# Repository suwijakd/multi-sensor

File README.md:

# Wearable multi-sensor logger (ESP32-C3)

Firmware + PC tooling to record four health sensors **simultaneously against a
single clock** and stream them to a CSV file with a live dashboard.

| Role | Part | Interface | How it's read |
|------|------|-----------|----------------|
| MCU  | ESP32-C3 Super Mini | — | native USB CDC serial |
| PPG  | DFRobot SEN0203 (Gravity Heart Rate) | **analog** | ADC1, raw waveform |
| IMU  | Adafruit ICM-20948 (9-DoF) | **I²C** | accel + gyro + mag |
| TEMP | MLX90614 / GY-906 | **I²C** | object + ambient °C |
| EDA  | Grove GSR v1.2 | **analog** | ADC1, raw signal |

The firmware samples PPG + GSR + IMU every tick (100 Hz by default) and the
slow MLX90614 on a decimated schedule (2 Hz, last value held), emitting one
timestamped CSV row per tick. Because every row shares the MCU's `micros()`
timebase, the channels are aligned with no cross-sensor drift.

> **Alternative sensor set:** a drop-in variant for a **GY-MAX30102** PPG and a
> **GY-521 / MPU-6050** IMU lives in
> [`arduino/multi_sensor_alt/`](arduino/multi_sensor_alt/). It emits the same
> CSV, so `record.py` works unchanged — just re-wire and flash that sketch. See
> its [README](arduino/multi_sensor_alt/README.md).

---

## 1. Wiring

**Power every sensor from `3V3` and `GND`** on the Super Mini. This keeps both
analog outputs within the ESP32-C3's 0–3.3 V ADC range — powering PPG/GSR from
5 V would clip the ADC at 4095.

| Sensor | Sensor pin | → ESP32-C3 pin | Notes |
|--------|-----------|----------------|-------|
| SEN0203 PPG | signal (`S`) | **GPIO0** | ADC1_CH0 |
| Grove GSR   | signal (`SIG`) | **GPIO1** | ADC1_CH1 |
| ICM-20948   | SDA | **GPIO5** | shared I²C |
| ICM-20948   | SCL | **GPIO6** | shared I²C |
| MLX90614    | SDA | **GPIO5** | shared I²C (addr `0x5A`) |
| MLX90614    | SCL | **GPIO6** | shared I²C |
| all         | VCC | **3V3** | |
| all         | GND | **GND** | common ground |

Both I²C breakouts (Adafruit ICM-20948, GY-906) have onboard pull-ups, so no
extra resistors are needed. The I²C bus runs at **100 kHz** — the MLX90614 is
SMBus and won't tolerate faster.

Pins are defined in [`arduino/multi_sensor/config.h`](arduino/multi_sensor/config.h); change them in one place.

---

## 2. Build & flash the firmware — pick one toolchain

The firmware lives in [`arduino/multi_sensor/`](arduino/multi_sensor/) as a
plain Arduino sketch. All three toolchains below compile that same folder, so
you only need one of them. **Board settings that matter in every case:** board
= *ESP32C3 Dev Module*, and **USB CDC On Boot = Enabled** (this is what makes
`Serial` the USB port on the Super Mini — without it the PC sees nothing).

> **Disk space:** the ESP32 compiler toolchain (~a few hundred MB) is needed by
> every option. The savings come from *how* it's managed: **arduino-cli** keeps
> one shared core under `~/.arduino15` with no per-project build tree, whereas
> PlatformIO stores a per-platform copy under `~/.platformio` (often 1–2 GB)
> plus a `.pio/` folder in each project. If you're tight on space, use Option B.

### Option A — Arduino IDE (GUI)

1. **Add ESP32 support:** *File → Preferences → Additional Boards Manager URLs*,
   add `https://espressif.github.io/arduino-esp32/package_esp32_index.json`,
   then *Tools → Board → Boards Manager* → install **esp32 by Espressif**.
2. **Libraries:** *Tools → Manage Libraries* → install **Adafruit ICM20X** and
   **Adafruit MLX90614 Library** (click *Install all* when it offers to add
   their dependencies, e.g. Adafruit BusIO + Unified Sensor).
3. Open `arduino/multi_sensor/multi_sensor.ino`.
4. *Tools* → Board = **ESP32C3 Dev Module**, **USB CDC On Boot = Enabled**,
   Port = your COM port → click **Upload**.

### Option B — arduino-cli (lightest, scriptable)

```bash
# one-time: install the shared ESP32 core (used by every sketch)
arduino-cli config init
arduino-cli config add board_manager.additional_urls https://espressif.github.io/arduino-esp32/package_esp32_index.json
arduino-cli core update-index
arduino-cli core install esp32:esp32

# one-time: libraries (dependencies are pulled in automatically)
arduino-cli lib install "Adafruit ICM20X" "Adafruit MLX90614 Library"

# build (from the project root) — the :CDCOnBoot=cdc flag = "USB CDC On Boot: Enabled"
arduino-cli compile --fqbn esp32:esp32:esp32c3:CDCOnBoot=cdc arduino/multi_sensor

# find the port, then flash
arduino-cli board list
arduino-cli upload -p COM5 --fqbn esp32:esp32:esp32c3:CDCOnBoot=cdc arduino/multi_sensor

# optional: watch the raw serial stream
arduino-cli monitor -p COM5 -c baudrate=115200
```

### Option C — PlatformIO

```bash
# from the project root (where platformio.ini lives)
pio run                 # build
pio run -t upload       # build + flash over USB
pio device monitor      # optional: watch the raw serial stream
```

`platformio.ini` sets `src_dir = arduino/multi_sensor` so PlatformIO builds the
same sketch; the USB-CDC build flags are already in there. In VS Code you can
use the ✓ (build) and → (upload) buttons instead.

**To reclaim PlatformIO's space later:** uninstall the PlatformIO VS Code
extension and delete the `~/.platformio` folder
(`C:\Users\<you>\.platformio`), or run `pio system prune -f` to clear caches.

---

**First upload tip (any option):** if the board isn't detected, hold **BOOT**,
tap/replug, then release, and upload again.

On boot the device prints a metadata block, e.g.:

```
# multi-sensor wearable logger
# sample_rate_hz=100 temp_rate_hz=2
# icm20948=ok mlx90614=ok
# units: ppg,gsr=adc_counts(0-4095) accel=m/s^2 gyro=rad/s mag=uT temp=degC t_us=micros
# columns: t_us,seq,ppg_raw,gsr_raw,ax,ay,az,gx,gy,gz,mx,my,mz,temp_obj_c,temp_amb_c
```

If a sensor reads `MISSING`, check wiring/address before recording (see
Troubleshooting).

---

## 3. Record on the PC

```bash
cd pc
python -m venv .venv && .venv\Scripts\activate    # Windows (use source .venv/bin/activate on macOS/Linux)
pip install -r requirements.txt

python record.py                              # autodetect port, log + live dashboard
python record.py --port COM14                 # specify the port
python record.py --no-plot                    # headless logging only
python record.py --labels "r=rest,a=active"   # marker keys (this is the default)
python record.py --list                       # list serial ports and exit
```

Close the dashboard window (or press `q`/Ctrl+C in `--no-plot` mode) to stop.
Files are written to `pc/recordings/session_YYYYMMDD_HHMMSS.csv`.

The dashboard shows PPG, GSR, the three accelerometer axes, and object/ambient
temperature. Gyro and magnetometer are still recorded to CSV — they're just not
plotted to keep the view readable.

### Event markers (rest / active, etc.)

Markers let you tag *when* conditions change so you can segment the data later.

- **With the dashboard:** click the plot window to focus it, then press a label
  key — `r` (rest) or `a` (active) by default — to begin that labelled state, or
  **space** for a one-off timestamp mark. A coloured dashed line + label appears
  at that instant on every panel.
- **Headless (`--no-plot`):** type the key and press **Enter** (`r`, `a`, or any
  full custom label like `squat`); **Enter** alone drops a one-off mark, `s`
  prints status, `q` quits.
- **Custom keys:** `--labels "r=rest,a=active,s=squat"`.

A "state" marker is *persistent*: every data row from then on carries that label
in its `label` column, so a typical rest/active protocol is just alternating
`r` and `a` presses at each transition.

### Guided protocol (auto-marked timing)

For a structured experiment, let the software run the schedule and mark the
transitions for you — no human reaction lag, identical timing every trial:

```bash
# 4 phases of 60 s each, auto-marked; live countdown in the plot title
python record.py --protocol "rest:60,active:60,rest:60,active:60"

# repeat a rest/squat block 5 times, headless
python record.py --no-plot --protocol "rest:30,active:30" --protocol-reps 5
```

- Each phase becomes a persistent `state` label, exactly like a manual press, so
  it lands in both the data `label` column and the events file.
- `--lead-in N` gives an N-second "get ready" countdown first (default 3 s).
- Recording **auto-stops when the protocol ends** (`--no-autostop` keeps it
  running); manual markers (`space`, label keys) still work during a protocol.

### Going wireless (Wi-Fi)

To cut the USB data cable, stream over Wi-Fi instead. Both firmware sketches
support it (off by default):

1. In the sketch's `config.h`, uncomment `#define STREAM_WIFI`, then re-flash.
   The device makes its own Wi-Fi network (SoftAP) — USB still works too.
2. Power the board from a small **USB battery bank** so it's fully untethered.
3. On the PC, join the device's Wi-Fi (`multisensor`, password `squat12345` by
   default — change both in `config.h`), then:

   ```bash
   python record.py --tcp 192.168.4.1:3333
   ```

Everything else — markers, the guided protocol, the dashboard, `analyze.py` — is
identical to the USB path; only the transport changes. The device's `t_us` clock
stays authoritative, so Wi-Fi jitter doesn't affect timing, and a dropped link
shows up as a `seq` gap (and stops the recording cleanly). PPG/GSR stay on ADC1,
which the radio doesn't disturb.

> **ESP32-C3 Super Mini note:** this board's power design can't drive the radio
> at full TX power, so the AP starts but the SSID is **invisible** even at close
> range. The firmware works around it by lowering TX power (`WIFI_TX_POWER` in
> `config.h`, default `WIFI_POWER_8_5dBm`); drop it to `WIFI_POWER_2dBm` if the
> SSID still doesn't show up. A board with a proper/external antenna doesn't need
> this. For a setup with no spare router, SoftAP needs
none; to instead keep the PC on your normal network, switch the firmware to
station mode (join an existing AP) — ask and I'll add the config for it.

---

## 4. Output files & schema

Each session writes two files: the per-sample data and a marker log.

**`session_*.csv`** — one row per sample. The PC adds `host_unix_time` (front)
and `label` (back); everything between is straight from the device.

| Column | Unit | Source |
|--------|------|--------|
| `host_unix_time` | seconds (PC clock) | added by `record.py` on receipt |
| `t_us` | microseconds (MCU clock) | authoritative inter-sample timing |
| `seq` | counter | gaps ⇒ dropped samples |
| `ppg_raw`, `gsr_raw` | ADC counts 0–4095 | analog sensors |
| `ax`,`ay`,`az` | m/s² | ICM-20948 accelerometer |
| `gx`,`gy`,`gz` | rad/s | ICM-20948 gyroscope |
| `mx`,`my`,`mz` | µT | ICM-20948 magnetometer |
| `temp_obj_c`, `temp_amb_c` | °C | MLX90614 (held at the 2 Hz cadence) |
| `label` | text | current marker state (empty until first marker) |

**`session_*_events.csv`** — one row per marker.

| Column | Meaning |
|--------|---------|
| `host_unix_time` | PC time the key was pressed |
| `t_us`, `seq` | the most recent sample at press time — join key into the data file |
| `type` | `state` (persistent label) or `mark` (one-off annotation) |
| `label` | e.g. `rest`, `active`, `squat`, `mark` |

Use `t_us` (not `host_unix_time`) for anything timing-sensitive like heart-rate
or HRV analysis — it's jitter-free relative to the host. To segment by
condition you can either filter the data file directly on `label`, or join the
events file on `seq`/`t_us`. PPG/GSR are stored raw so you keep full fidelity;
convert to volts on the PC with `volts = counts / 4095 * 3.3`.

---

## 5. Analysis (post-processing)

Turn recorded sessions into physiological measures offline with
[`pc/analyze.py`](pc/analyze.py) (extra deps: `pip install -r
pc/requirements-analysis.txt`). It batch-processes a folder, segmenting each
session by its `label` column:

```bash
cd pc
python analyze.py                       # processes ./recordings
python analyze.py --indir recordings --outdir results
python analyze.py --squat-prominence 2.0 --no-plots
```

Per run it writes, into `<indir>/analysis/`:

- **`analysis_phases.csv`** — one row per phase per session: `hr_mean`,
  `hr_peak`, `rmssd_ms`, `sdnn_ms`, `reps`, `cadence_spm`, `motion_ms2`.
- **`analysis_summary.csv`** — one row per session: baseline HR/RMSSD, active
  HR mean/peak, total reps, and **HRR60** (heart-rate recovery).
- **`<session>_qa.png`** — PPG + detected beats, accel + detected squats, and an
  HR timeline, so you can verify detections before trusting the numbers.

Notes:

- HR comes from PPG, squat reps/cadence from the accelerometer, RMSSD from
  inter-beat intervals. **HR/RMSSD are only reliable on low-motion phases**
  (rest / recovery) — the `motion_ms2` column flags how stationary each phase is.
- Squat counting detects accel-magnitude peaks; check the QA figure and tune
  `--squat-prominence` (m/s²) / `--squat-min-interval` (s) to your squat style.
- Works on either firmware variant (same columns).

---

## 6. Tuning

Edit [`arduino/multi_sensor/config.h`](arduino/multi_sensor/config.h) and re-flash:

- `SAMPLE_RATE_HZ` — base rate. 100 Hz is comfortable for PPG/HR and IMU motion;
  the 100 kHz I²C bus and ICM magnetometer cap practical rates near ~100–150 Hz.
- `TEMP_RATE_HZ` — MLX90614 read cadence (it changes slowly; 1–2 Hz is plenty).
- `ICM_ADDR` — `0x69` default; set `0x68` if the ICM-20948's ADR pin is tied low.

---

## 7. Troubleshooting

- **`icm20948=MISSING`** — wrong address (try `0x68`), or SDA/SCL swapped.
- **`mlx90614=MISSING` or temp = `nan`/`-273`** — I²C wiring/pull-ups, or the
  bus crept above 100 kHz.
- **PPG/GSR pinned at 4095** — sensor powered from 5 V; move it to 3V3.
- **No data / garbage on the PC** — the firmware must be built with USB CDC on
  boot: *USB CDC On Boot = Enabled* in Arduino IDE, `:CDCOnBoot=cdc` in the
  arduino-cli FQBN, or the `ARDUINO_USB_CDC_ON_BOOT` flag (already in
  `platformio.ini`). Also confirm you opened the right port. The board may reset
  when the port opens — you'll see the `#` banner reprint, which is normal.
- **`txdrop` climbing in `# stats`** (and nonzero `dropped` on the PC) — the PC
  isn't draining the USB port fast enough, so the device dropped whole rows to
  keep the sample clock steady. The data that *did* arrive is uniformly timed.
  Reduce the host load (e.g. run `--no-plot`, or widen `--window` less) or raise
  the device TX buffer (`Serial.setTxBufferSize`).
- **A big `dropped` count *at startup* / first samples look old** — the C3 is
  not reset by opening the port, so a board left powered keeps running and its
  TX buffer holds a stale prefix. `record.py` drains it on connect
  (`--flush-seconds`, default 0.5 s), so the recording starts on live data.
  Note the device's `txdrop` in `# stats` is cumulative since power-on and won't
  reset until you power-cycle the board — the PC summary's `dropped` is the
  session-accurate figure.
- **`overruns` climbing in `# stats`** — the sampling tick itself can't finish
  in time (not a USB issue); lower `SAMPLE_RATE_HZ`.
- **Wrong COM port chosen** — `python record.py --list`, then pass `--port`.

---

## Layout

```
platformio.ini                 PlatformIO config (points src_dir at the sketch)
arduino/
  multi_sensor/
    multi_sensor.ino           sampling loop + CSV-over-USB output
    config.h                   pin map, sample rates, I2C settings
pc/
  record.py                    serial -> CSV logger + live dashboard
  requirements.txt
```

The firmware is one Arduino sketch built by any of Arduino IDE, arduino-cli, or
PlatformIO — there's a single copy of the code, not one per toolchain.

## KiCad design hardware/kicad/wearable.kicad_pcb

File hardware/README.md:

# Hardware — rev A

Plan and part choices: [PLAN.md](PLAN.md). This folder holds the rev A schematic, the
routed 36 × 42 mm board, the case and the manufacturing files.

| Path | What |
|---|---|
| `tools/gen_schematic.py` | **The circuit.** Every part, value, footprint and pin→net. Edit this, not the `.kicad_sch` files. |
| `tools/customlib.py`, `tools/footprints.py` | Symbols and footprints KiCad doesn't ship. |
| `tools/kicadgen.py`, `tools/sexpr.py` | Schematic generator (labels on every pin, no hand-drawn wires). |
| `tools/verify_netlist.py` | Checks KiCad's exported netlist pin-by-pin against the design. |
| `tools/board_geometry.py` | **The mechanical numbers** shared by the board and the case: outline, connector and sensor positions, battery. |
| `tools/gen_pcb.py` | **The board.** Placement table, outline, keep-outs, planes, plane vias, autorouting (Freerouting 1.9.0) and import. Run with KiCad's Python. |
| `tools/gen_case.py`, `tools/preview_case.py` | **The case.** Bottom shell and lid as STL, an interference check against the placed parts, and preview images. |
| `tools/export_fab.py` | Runs DRC, then writes Gerbers, drill, placement, BOM, renders and STEP into `fab/`. |
| `kicad/` | Generated KiCad 10 project: schematic sheets, `wearable.kicad_pcb`, project libraries. |
| `case/` | `bottom_shell.stl`, `lid.stl`, `case_preview.png`. |
| `fab/` | Manufacturing outputs (see below). |
| `datasheets/` | Put vendor PDFs here (not committed). |

## Regenerate and check

```bash
KPY="<KiCad>/bin/python.exe"     # KiCad's own Python, it provides pcbnew
python hardware/tools/footprints.py
python hardware/tools/gen_schematic.py
kicad-cli sch erc --severity-all hardware/kicad/wearable.kicad_sch
kicad-cli sch export netlist --format kicadsexpr -o hardware/kicad/wearable.net hardware/kicad/wearable.kicad_sch
python hardware/tools/verify_netlist.py hardware/kicad/wearable.net
"$KPY" hardware/tools/gen_pcb.py route     # place, fan out power pads, autoroute, import, fill
"$KPY" hardware/tools/gen_pcb.py dump      # part boxes for the case fit check
python hardware/tools/export_fab.py        # DRC gate + manufacturing files
python hardware/tools/preview_case.py      # case STLs, fit check, preview (needs manifold3d, trimesh, matplotlib)
```

Status on 2026-11-11:
- **Schematic:** ERC 0 errors, 0 warnings. Netlist check: 56 nets and 276 pins match the design.
- **Board:** fully routed. KiCad DRC with schematic parity: **0 violations, 0 unconnected
  nets, 0 parity issues.** 4 layers, 1.0 mm, 83 footprints (74 fitted), about 1.3 m of
  track and 159 vias.
- **Case:** both parts watertight; no interference between the case and any placed part
  or the battery.
- **Pinouts:** all 5 custom symbols checked against the vendor datasheets.

## Board

- **Stack-up:** F.Cu signals + GND pour, In1 solid GND plane, In2 solid +1V8 plane,
  B.Cu signals + GND pour.
- **Rules:** 0.127 mm tracks / 0.1 mm clearance (needed between the module's staggered
  pads and at the 0.4 mm-pitch charger), power nets 0.25 mm, vias 0.45/0.2 mm and
  0.5/0.25 mm, 0.3 mm copper-to-edge.
- **Antenna:** the module sits at the Y = 0 edge. No copper on any layer in a strip
  27 mm wide by 3.75 mm deep under and beside the antenna.
- **Top side:** everything except the two skin sensors. Parts under the battery are at
  most 2.1 mm tall.
- **Skin side:** MAXM86161 at the board centre, TMP117 inside a pour-free 4 × 4 mm area,
  six SWD test pads (GND, 1V8, DIO, CLK, RST, SWO) at 2.54 mm pitch.
- **Electrodes:** two plated M2 holes, 29 mm apart. E2 (sense) is on the jack side, E1
  (driven) on the USB side.
- **Corners:** 4.4 mm notches for the case's screw posts.
- **How it was routed:** `gen_pcb.py` gives every GND and +1V8 pad its own via to the
  plane first and locks those, then Freerouting routes the signals around them. Routing
  is autorouted, not hand-tuned: it passes DRC, but see "Review before ordering".

## Case

Two printed parts, sized for an ordered SLA or MJF print (1.4 mm walls, 1.2 mm lid).
Outside: 39.4 × 57.0 × 11.6 mm including the strap bars (45.4 mm long without them).

- **Bottom shell:** the board sits on the floor, held by the two electrode screws. Openings:
  PPG window, TMP117 pocket with a 5 mm recess for a metal contact disc, two electrode
  screw holes, USB-C notch, electrode-jack notch. A 3 mm round bar at each end takes a
  20 mm strap.
- **Lid:** ribs hold the 502030 cell 2.4 mm above the board. A flexing tab with a post
  presses the USER switch, a pinhole reaches RESET, and a tube over the LED ends in a
  1.6 mm hole.
- **Hardware:** 4 × M2×8 self-tapping screws (lid), 2 × stainless M2×5 pan-head screws
  with nuts (electrodes), thin double-sided tape for the battery.
- **Heights above the skin:** board 1.55–2.55 mm, lid joint 6.2 mm, battery 4.95–9.95 mm,
  top 11.6 mm. The PPG face sits 0.15 mm inside the floor.

## Manufacturing files (`fab/`)

| File | Use |
|---|---|
| `wearable_revA_gerbers.zip` | Gerbers for all 4 copper layers, mask, paste, silkscreen, outline, plus PTH and NPTH drill files. |
| `wearable_revA_cpl.csv` | Component placement in JLCPCB's column layout (72 top, 2 bottom). |
| `wearable_revA_bom.csv` | BOM in JLCPCB's column layout. **The LCSC column is still empty.** |
| `wearable_revA_schematic.pdf`, `board_top.png`, `board_bottom.png`, `wearable_revA_board.step` | Reference. |

Order settings: 4 layers, 1.0 mm, ENIG (the electrode and test pads are bare), assembly
on both sides.

## Review before ordering

1. **LCSC part numbers and stock** for all 48 BOM lines. The MAXM86161, MDBT50Q and
   BQ25180 may not be stocked by JLCPCB and may need to be consigned or hand-soldered.
2. **Fab capability:** 0.2 mm via drills, 0.1 mm clearance and the 0.4 mm-pitch BQ25180
   are inside JLCPCB's published 4-layer limits but can add cost. Confirm when quoting.
3. **Placement rotations** in JLCPCB's preview: their rotation convention differs from
   KiCad's for some packages.
4. **A look at the routing in KiCad:** the crystal traces are 9–10 mm and power runs at
   0.25 mm width. Both are workable; an experienced eye may want to tidy them.
5. **RF:** antenna performance on the wrist is not simulated or measured. Raytac offers a
   free layout review.
6. **Case:** not printed yet. Clearances are 0.3 mm around the board and 0.15 mm around
   the PPG, and the button tab and strap bars are untested.
7. **PPG window:** the opening follows the package body. The LED and photodiode positions
   from outline 21-100309 are still not checked.
8. **Battery polarity:** pad 1 (marked +) is battery positive. A reversed cell destroys
   the charger.

## Blocks

- **Power:** USB-C (5.1 kΩ Rd, USBLC6 ESD) → **BQ25180** charger with power path → `VSYS` (3.0–4.5 V)
  → **TPS62840** buck → `+1V8`, which powers *all* logic. **MAX17048** gauge on `VBAT`.
  10 k NTC on TS. Two solder pads for the battery leads. Test points on every rail.
- **MCU:** **MDBT50Q-1MV2** (nRF52840) in normal-voltage mode (VDD = VDDH = 1.8 V). 32.768 kHz
  crystal. **W25Q128JW** 16 MB 1.8 V QSPI flash. 2.2 kΩ I²C pull-ups, 47 kΩ pull-ups on the
  open-drain interrupts. Six SWD test pads on the skin side (use a 2.54 mm pogo clip).
  Reset + user buttons. Common-anode RGB LED on VSYS through 1.8 V-drivable FETs.
  **Pins follow the Adafruit Feather nRF52840 Express** (QSPI P0.17/19–23, SDA P0.12, SCL
  P0.11, button P1.02, LEDs P1.15/P1.10/P0.16), so its UF2 bootloader and Arduino variant
  work for first bring-up.
- **Sensors (one 400 kHz I²C bus):** MAXM86161 0x62, BMI270 0x68, TMP117 0x48,
  BQ25180 0x6A, MAX17048 0x36. No address conflicts. Every device's VIH is ≤ 1.4 V, so
  1.8 V pull-ups work for all of them.
- **PPG:** the MAXM86161 is single-supply. It runs from VLED = VSYS (3.0–5.5 V) and makes
  its own 1.8 V internally (VLDO), so it never loads `+1V8`. LDO_EN is driven by
  `PPG_EN` (P0.13) with a 100 k pull-down, so the module is fully off (≈0.05 µA) until
  firmware enables it. Pins 6–8 are the LED driver nodes: soldered down, connected to
  nothing. The MAXM86161A is a drop-in alternative (same pinout and land pattern).
- **EDA:** a 909k/499k/402k 0.1 % divider gives 0.90 V (TIA reference) and 0.40 V
  (excitation), so the skin sees 0.50 V. LPV812 half A holds electrode E1 at 0.40 V, with
  the loop closed at the electrode so the 10 kΩ protection resistor causes no error. Half B
  is a TIA: 392 kΩ for 0–4.3 µS, plus 43.2 kΩ switched in by TS5A3166 for 0–44 µS. The ADC
  reads EDA_OUT, EDA_VREF and EDA_VEXC_SET, which allows ratiometric calibration. The
  electrodes are two stainless M2 screws through the case floor, with a JST-SH jack for
  finger electrodes and TPD1E05U06 ESD diodes.

### nRF52840 pin map

| Pin | Net | Pin | Net |
|---|---|---|---|
| P0.00/P0.01 | 32 kHz crystal | P0.04 (AIN2) | EDA_OUT |
| P0.11 / P0.12 | I2C_SCL / I2C_SDA | P0.05 (AIN3) | EDA_VREF |
| P0.17,22,23,21 | QSPI IO0–IO3 | P0.30 (AIN6) | EDA_VEXC_SET |
| P0.19 / P0.20 | QSPI SCK / CS | P1.08 | EDA_RANGE |
| P0.18 | nRESET | P0.07 | PPG_INT |
| P1.00 | SWO | P0.26 / P0.27 | IMU_INT1 / INT2 |
| P1.02 | BTN_USER | P0.06 | GAUGE_ALRT |
| P1.15 / P0.16 / P1.10 | LED R / G / B | P0.08 | CHG_INT |
| P0.02,03,28,31,24,25 | not connected | P1.09 | TEMP_ALERT |
| P0.13 | PPG_EN (MAXM86161 LDO_EN) | | |

## Datasheet verification (2026-11-09)

| Part | Checked | Result / change |
|---|---|---|
| BQ25180 | Table 6-1, §9.2, YBG0008 drawing | Ball map **corrected** (A1 /INT, A2 IN, B1 SCL, B2 SYS, C1 SDA, C2 BAT, D1 TS/MR, D2 GND). TS biased internally (38 µA): NTC only. IN 1–10 µF and SYS 10 µF, both 25 V rated. VIH 1.3 V. Footprint drawn: 0.4 mm pitch, all balls on the perimeter. |
| TPS62840 | Pin Functions (DLC), Table 1, Table 2 | Pin order **corrected** (1 GND, 2 VIN, 3 MODE, 4 EN, 5 VSET, 6 STOP, 7 SW, 8 VOS). VSET to GND = 1.8 V, so R3 = 0 Ω. Inductor changed to the datasheet part DFE201612E-2R2M. |
| MAXM86161 | Pin Description, app circuit, layout guide | Pinout **corrected**. It's single-supply (VLED + internal LDO), with VLDO/VREF 1 µF each and VLED 10 µF. LDO_EN is now on a GPIO. VIH 1.4 V. |
| MAX17048 | Pin table (TDFN), EC table | Pinout confirmed. VIH 1.4 V. KiCad footprint drawn from Maxim 21-0168. |
| BMI270 | Table 22 | Pinout identical to the BMI160. Unused ASDx/ASCx/OCSB/OSDO may be left unconnected (never tied to GND). |
| MDBT50Q-1MV2 | §8 reference circuits | Normal-voltage mode confirmed (VDDH = VDD, DCCH open). 12 pF crystal caps match. Raytac shows 27 Ω on D+/D−, so R25/R26 were added as 0 Ω options. |

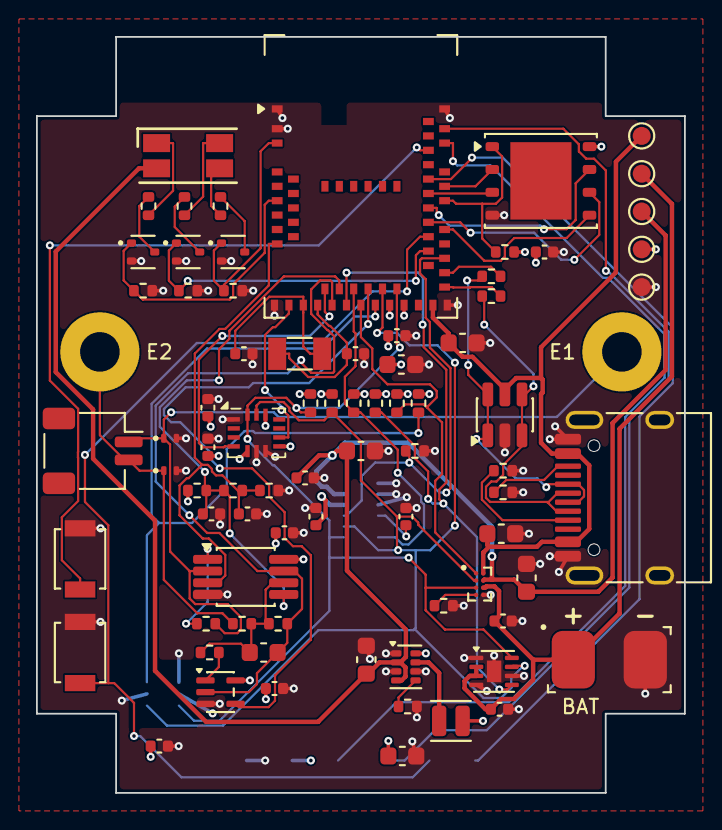
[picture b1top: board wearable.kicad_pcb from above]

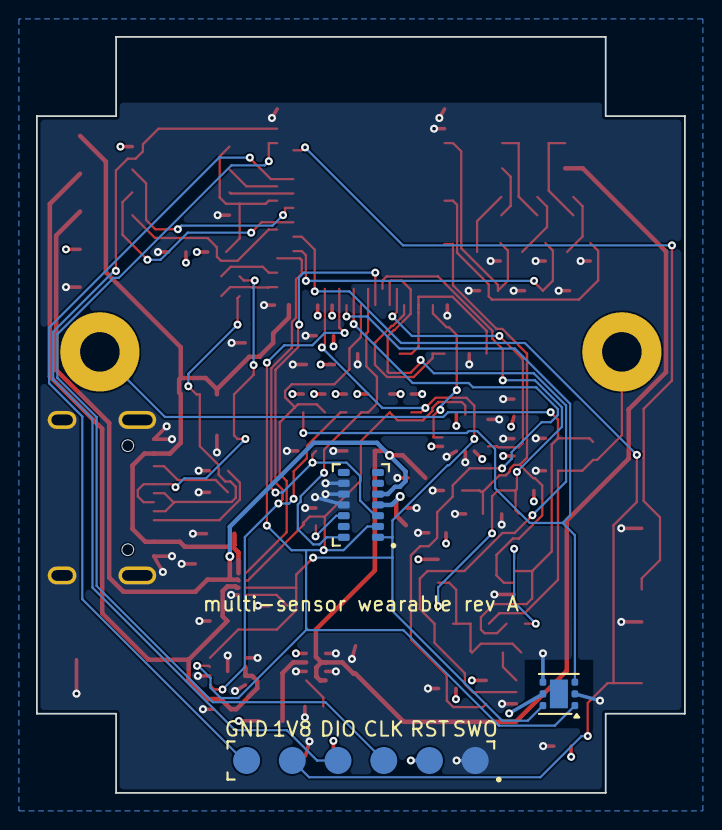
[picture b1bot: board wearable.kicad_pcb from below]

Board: 4 copper layers, 36.0 x 42.0 mm, 83 parts (3 on the bottom side), 56 nets.

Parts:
C1: 4.7u 25V; C_0603_1608Metric
C2: 10u 25V; C_0603_1608Metric
C3, C13, C24: 1u; C_0402_1005Metric
C4, C8, C12, C15, C16, C17, C18, C19, C20, C21, C23: 100n; C_0402_1005Metric
C5, C9: 4.7u; C_0603_1608Metric
C6, C7, C14: 10u; C_0603_1608Metric
C10, C11: 12p; C_0402_1005Metric
C22: 10n C0G; C_0603_1608Metric
D1: RGB CA; LED_RGB_1210
D2, D3: TPD1E05U06; Texas_DPY0002A_0.6x1mm_P0.65mm
E1: EDA_E1; MountingHole_2.2mm_M2_Pad
E2: EDA_E2; MountingHole_2.2mm_M2_Pad
J1: USB-C; USB_C_Receptacle_HRO_TYPE-C-31-M-12
J2: LiPo pads; BatteryPads_1x02_P4.0mm
J3: SWD pads; TestPads_1x06_P2.54mm
J5: EDA ext; JST_SH_SM02B-SRSS-TB_1x02-1MP_P1.00mm_Horizontal
L1: 2.2u; L_Changjiang_FTC201612S
Q1, Q2, Q3: DMG1012T; SOT-523
R1, R2: 5.1k; R_0402_1005Metric
R3, R25, R26: 0; R_0402_1005Metric
R4, R14, R15, R16, R24: 100k; R_0402_1005Metric
R5, R6: 2.2k; R_0402_1005Metric
R7, R8, R9, R10: 47k; R_0402_1005Metric
R11: 1.5k; R_0402_1005Metric
R12, R13: 470; R_0402_1005Metric
R17: 909k 0.1%; R_0402_1005Metric
R18: 499k 0.1%; R_0402_1005Metric
R19: 402k 0.1%; R_0402_1005Metric
R20: 10k; R_0402_1005Metric
R21: 1k; R_0402_1005Metric
R22: 392k 0.1%; R_0402_1005Metric
R23: 43.2k 0.1%; R_0402_1005Metric
SW1: RESET; SW_SPST_B3U-1000P
SW2: USER; SW_SPST_B3U-1000P
TH1: 10k B3435; R_0402_1005Metric
TP1: VBUS; TestPoint_Pad_D1.0mm
TP2: VBAT; TestPoint_Pad_D1.0mm
TP3: VSYS; TestPoint_Pad_D1.0mm
TP4: +1V8; TestPoint_Pad_D1.0mm
TP5: GND; TestPoint_Pad_D1.0mm
U1: MDBT50Q-1MV2; Raytac_MDBT50Q
U2: USBLC6-2SC6; SOT-23-6
U3: BQ25180; TI_YBG0008_DSBGA-8_1.6x1.1mm
U4: MAX17048; TDFN-8-1EP_2x2mm_P0.5mm_EP0.8x1.2mm
U5: TPS62840; VSON-8_1.5x2mm_P0.5mm
U6: W25Q128JW; WSON-8-1EP_6x5mm_P1.27mm_EP3.4x4.3mm
U7: MAXM86161; MAXM86161_OLGA-14_2.9x4.3mm
U8: BMI270; Bosch_LGA-14_3x2.5mm_P0.5mm
U9: TMP117; WSON-6-1EP_2x2mm_P0.65mm_EP1x1.6mm
U10: LPV812; VSSOP-8_3x3mm_P0.65mm
U11: TS5A3166; SOT-353_SC-70-5
Y1: 32.768k 9pF; Crystal_SMD_3215-2Pin_3.2x1.5mm

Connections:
+1V8: C6.1, C7.1, C8.1, C12.1, C16.1, C17.1, C18.1, C21.1, C23.1, J3.2, L1.2, R4.2, R5.2, R6.2, R7.2, R8.2, R9.2, R10.2, R17.1, TP4.1, U1.28, U1.30, U5.8, U6.8, U8.5, U8.8, U8.12, U9.5, U10.8, U11.5
/EDA/EDA_E1: D2.1, E1.1, J5.1, R20.2, U10.2
/EDA/EDA_E1_DRV: R20.1, U10.1
/EDA/EDA_E2: D3.1, E2.1, J5.2, R21.1
/EDA/EDA_RSW: R23.2, U11.1
/EDA/EDA_TIA_IN: C22.1, R21.2, R22.1, R23.1, U10.6
/MCU/BTN_USER: SW2.1, U1.50
/MCU/LED_B: Q3.1, R16.1, U1.3
/MCU/LED_BD: Q3.3, R13.2
/MCU/LED_BK: D1.3, R13.1
/MCU/LED_G: Q2.1, R15.1, U1.38
/MCU/LED_GD: Q2.3, R12.2
/MCU/LED_GK: D1.4, R12.1
/MCU/LED_R: Q1.1, R14.1, U1.8
/MCU/LED_RD: Q1.3, R11.2
/MCU/LED_RK: D1.1, R11.1
/MCU/QSPI_CS: R4.1, U1.44, U6.1
/MCU/QSPI_IO0: U1.41, U6.5
/MCU/QSPI_IO1: U1.46, U6.2
/MCU/QSPI_IO2: U1.45, U6.3
/MCU/QSPI_IO3: U1.43, U6.7
/MCU/QSPI_SCK: U1.42, U6.6
/MCU/SWDCLK: J3.4, U1.53
/MCU/SWDIO: J3.3, U1.51
/MCU/SWO: J3.6, U1.47
/MCU/XL1: C10.1, U1.17, Y1.1
/MCU/XL2: C11.1, U1.18, Y1.2
/MCU/nRESET: J3.5, SW1.1, U1.40
/Power/BUCK_SW: L1.1, U5.7
/Power/BUCK_VSET: R3.1, U5.5
/Power/CC1: J1.A5, R1.1
/Power/CC2: J1.B5, R2.1
/Power/CHG_TS: TH1.1, U3.D1
/Power/USB_DM_C: J1.A7, J1.B7, R26.1, U2.3, U2.4
/Power/USB_DP_C: J1.A6, J1.B6, R25.1, U2.1, U2.6
/Sensors/PPG_VLDO: C13.1, U7.4
/Sensors/PPG_VREF: C24.1, U7.12
CHG_INT: R9.1, U1.24, U3.A1
EDA_OUT: C22.2, R22.2, U1.20, U10.7, U11.2
EDA_RANGE: U1.25, U11.4
EDA_VEXC_SET: C20.1, R18.2, R19.1, U1.14, U10.3
EDA_VREF: C19.1, R17.2, R18.1, U1.21, U10.5
GAUGE_ALRT: R8.1, U1.22, U4.5
GND: C1.2, C2.2, C3.2, C4.2, C5.2, C6.2, C7.2, C8.2, C9.2, C10.2, C11.2, C12.2, C13.2, C14.2, C15.2, C16.2, C17.2, C18.2, C19.2, C20.2, C21.2, C23.2, C24.2, D2.2, D3.2, J1.A1, J1.A12, J1.B1, J1.B12, J1.SH, J2.2, J3.1, Q1.2, Q2.2, Q3.2, R1.2, R2.2, R3.2, R14.2, R15.2, R16.2, R19.2, R24.2, SW1.2, SW2.2, TH1.2, TP5.1, U1.1, U1.2, U1.15, U1.33, U1.55, U2.2, U3.D2, U4.1, U4.4, U4.6, U4.9, U5.1, U5.3, U5.6, U6.4, U7.9, U7.10, U7.11, U8.1, U8.6, U8.7, U9.2, U9.4, U10.4, U11.3
I2C_SCL: R6.1, U1.27, U3.B1, U4.7, U7.2, U8.13, U9.1
I2C_SDA: R5.1, U1.29, U3.C1, U4.8, U7.1, U8.14, U9.6
IMU_INT1: U1.19, U8.4
IMU_INT2: U1.16, U8.9
PPG_EN: R24.1, U1.37, U7.3
PPG_INT: R7.1, U1.23, U7.14
TEMP_ALERT: R10.1, U1.26, U9.3
USB_DM: R26.2, U1.34
USB_DP: R25.2, U1.35
VBAT: C3.1, C4.1, J2.1, TP2.1, U3.C2, U4.2, U4.3
VBUS: C1.1, C9.1, J1.A4, J1.A9, J1.B4, J1.B9, TP1.1, U1.32, U2.5, U3.A2
VSYS: C2.1, C5.1, C14.1, C15.1, D1.2, TP3.1, U3.B2, U5.2, U5.4, U7.5

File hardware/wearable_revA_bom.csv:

"Refs","Value","Footprint","MPN","Manufacturer","LCSC","Qty","DNP","Note"
"C1","4.7u 25V","Capacitor_SMD:C_0603_1608Metric","","","","1","","BQ25180 IN: 1-10 uF, 25 V rated. Total VBUS capacitance with C9 stays under the USB 10 uF limit"
"C2","10u 25V","Capacitor_SMD:C_0603_1608Metric","","","","1","","SYS: 10 uF nominal, >1 uF after DC-bias derating"
"C3,C13,C24","1u","Capacitor_SMD:C_0402_1005Metric","","","","3","","VLDO bypass, 1 uF to GND_ANA,VREF bypass, 1 uF to GND_ANA"
"C4,C8,C12,C15,C16,C17,C18,C19,C20,C21,C23","100n","Capacitor_SMD:C_0402_1005Metric","","","","11","","VDD,VDDIO"
"C5,C9","4.7u","Capacitor_SMD:C_0603_1608Metric","","","","2","","CIN: 4.7 uF required at VIN,nRF52840 VBUS decoupling"
"C6,C7,C14","10u","Capacitor_SMD:C_0603_1608Metric","","","","3","","VLED bypass: 10 uF to PGND, close to pin 5"
"C10,C11","12p","Capacitor_SMD:C_0402_1005Metric","","","","2","","C0G,C0G. C = 2*CL - Cpcb - Cpin"
"C22","10n C0G","Capacitor_SMD:C_0603_1608Metric","","","","1","",""
"D1","RGB CA","LED_SMD:LED_RGB_1210","","","","1","","Common anode. Green/blue need more than 1.8 V, so the LED runs from VSYS"
"D2,D3","TPD1E05U06","Package_SON:Texas_DPY0002A_0.6x1mm_P0.65mm","TPD1E05U06DPYR","TI","","2","","Electrode ESD,Electrode ESD. Leakage adds to the measured current: check the datasheet at 0.9 V"
"E1","EDA_E1","TestPoint:TestPoint_Pad_D2.0mm","","","","1","",""
"E2","EDA_E2","TestPoint:TestPoint_Pad_D2.0mm","","","","1","",""
"J1","USB-C","Connector_USB:USB_C_Receptacle_HRO_TYPE-C-31-M-12","TYPE-C-31-M-12","HRO","","1","",""
"J2","LiPo","Connector_JST:JST_PH_S2B-PH-SM4-TB_1x02-1MP_P2.00mm_Horizontal","S2B-PH-SM4-TB","JST","","1","","Battery with built-in protection (PCM). CHECK POLARITY: JST-PH battery pinouts vary by vendor"
"J3","SWD","Connector_PinHeader_1.27mm:PinHeader_2x05_P1.27mm_Vertical_SMD","","","","1","","Probe must support 1.8 V targets (e.g. J-Link). Not a 3.3 V-only probe"
"J5","EDA ext","Connector_JST:JST_SH_SM02B-SRSS-TB_1x02-1MP_P1.00mm_Horizontal","SM02B-SRSS-TB","JST","","1","","Finger electrodes for stronger EDA than the wrist"
"L1","2.2u","Inductor_SMD:L_Changjiang_FTC201612S","DFE201612E-2R2M=P2","Murata","","1","","Datasheet reference part: 2.2 uH, 116 mOhm, 2016"
"Q1,Q2,Q3","DMG1012T","Package_TO_SOT_SMD:SOT-523","DMG1012T-7","Diodes Inc","","3","","Vgs(th) <= 1.0 V, so 1.8 V GPIO drive is enough"
"R1,R2","5.1k","Resistor_SMD:R_0402_1005Metric","","","","2","","UFP Rd pull-down: 5 V default USB power"
"R3,R25,R26","0","Resistor_SMD:R_0402_1005Metric","","","","3","","Raytac MDBT50Q USB reference fits 27R here; Nordic's nRF52840 reference uses none. Start with 0R,See R25,VSET=GND selects 1.8 V (datasheet Table 1). Fit an E96 resistor here to change VOUT. <100 pF on VSET"
"R4,R14,R15,R16,R24","100k","Resistor_SMD:R_0402_1005Metric","","","","5","","Keeps the LED off during reset,Module stays in shutdown (LDO off) until firmware drives PPG_EN high"
"R5,R6","2.2k","Resistor_SMD:R_0402_1005Metric","","","","2","",""
"R7,R8,R9,R10","47k","Resistor_SMD:R_0402_1005Metric","","","","4","",""
"R11","1.5k","Resistor_SMD:R_0402_1005Metric","","","","1","",""
"R12,R13","470","Resistor_SMD:R_0402_1005Metric","","","","2","",""
"R17","909k 0.1%","Resistor_SMD:R_0402_1005Metric","","","","1","",""
"R18","499k 0.1%","Resistor_SMD:R_0402_1005Metric","","","","1","",""
"R19","402k 0.1%","Resistor_SMD:R_0402_1005Metric","","","","1","","Skin sees 0.90 - 0.40 = 0.50 V"
"R20","10k","Resistor_SMD:R_0402_1005Metric","","","","1","","Inside the buffer loop, so no voltage error"
"R21","1k","Resistor_SMD:R_0402_1005Metric","","","","1","","Series protection. Firmware corrects the I*R drop"
"R22","392k 0.1%","Resistor_SMD:R_0402_1005Metric","","","","1","","High-sensitivity range: 0-2.2 uA (0-4.3 uS)"
"R23","43.2k 0.1%","Resistor_SMD:R_0402_1005Metric","","","","1","","Switched in parallel: 0-22 uA (0-44 uS)"
"SW1","RESET","Button_Switch_SMD:SW_SPST_B3U-1000P","B3U-1000P","Omron","","1","","Double-tap enters the UF2 bootloader"
"SW2","USER","Button_Switch_SMD:SW_SPST_B3U-1000P","B3U-1000P","Omron","","1","",""
"TH1","10k B3435","Resistor_SMD:R_0402_1005Metric","NCP15XH103F03RC","Murata","","1","","TS is biased internally (38 uA). Place against the battery; Kelvin GND to U3 GND"
"TP1","VBUS","TestPoint:TestPoint_Pad_D1.0mm","","","","1","",""
"TP2","VBAT","TestPoint:TestPoint_Pad_D1.0mm","","","","1","",""
"TP3","VSYS","TestPoint:TestPoint_Pad_D1.0mm","","","","1","",""
"TP4","+1V8","TestPoint:TestPoint_Pad_D1.0mm","","","","1","",""
"TP5","GND","TestPoint:TestPoint_Pad_D1.0mm","","","","1","",""
"U1","MDBT50Q-1MV2","RF_Module:Raytac_MDBT50Q","MDBT50Q-1MV2","Raytac","","1","","Normal-voltage mode: VDD=VDDH=1.8 V from the buck, DCCH unused. Antenna keep-out per Raytac datasheet"
"U2","USBLC6-2SC6","Package_TO_SOT_SMD:SOT-23-6","USBLC6-2SC6","ST","","1","",""
"U3","BQ25180","wearable:TI_YBG0008_DSBGA-8_1.6x1.1mm","BQ25180YBGR","TI","","1","","I2C 0x6A. Program ICHG for the cell (<=1C). Ship mode exits on USB plug-in or a TS/MR low pulse"
"U4","MAX17048","Package_DFN_QFN:TDFN-8-1EP_2x2mm_P0.5mm_EP0.8x1.2mm","MAX17048G+T10","Analog Devices","","1","","I2C 0x36"
"U5","TPS62840","Package_SON:VSON-8_1.5x2mm_P0.5mm","TPS62840DLCR","TI","","1","","MODE=GND: auto power-save. STOP=GND: normal operation. EN/STOP have internal pull-downs"
"U6","W25Q128JW","Package_SON:WSON-8-1EP_6x5mm_P1.27mm_EP3.4x4.3mm","W25Q128JWPIQ","Winbond","","1","","1.8 V part (JW). Symbol is the pin-identical JV"
"U7","MAXM86161","wearable:MAXM86161_OLGA-14_2.9x4.3mm","MAXM86161EFD+","Analog Devices","","1","","I2C 0x62, VIH 1.4 V. Single supply VLED 3.0-5.5 V. Pins 6-8: solder, connect to nothing. MAXM86161AEFD+ is a drop-in alternative. Bottom side, under the case window"
"U8","BMI270","Package_LGA:Bosch_LGA-14_3x2.5mm_P0.5mm","BMI270","Bosch","","1","","CSB high = I2C. SDO low = address 0x68"
"U9","TMP117","Package_SON:WSON-6-1EP_2x2mm_P0.65mm_EP1x1.6mm","TMP117AIDRVR","TI","","1","","On an isolated board tab with a thermal pad to a stainless contact disc"
"U10","LPV812","Package_SO:VSSOP-8_3x3mm_P0.65mm","LPV812DGKR","TI","","1","",""
"U11","TS5A3166","Package_TO_SOT_SMD:SOT-353_SC-70-5","TS5A3166DCKR","TI","","1","","EDA_RANGE high = low-gain range"
"Y1","32.768k 9pF","Crystal:Crystal_SMD_3215-2Pin_3.2x1.5mm","FC-135 32.768kHz 9pF","Epson","","1","",""

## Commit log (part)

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2026-06-13 Revert "Add experiment event markers + fix dashboard/sample-rate reliability"
